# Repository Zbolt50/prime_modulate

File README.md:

# prime_modulate
Firmware for prime_modulate- a split keyboard that has it all, and then more.

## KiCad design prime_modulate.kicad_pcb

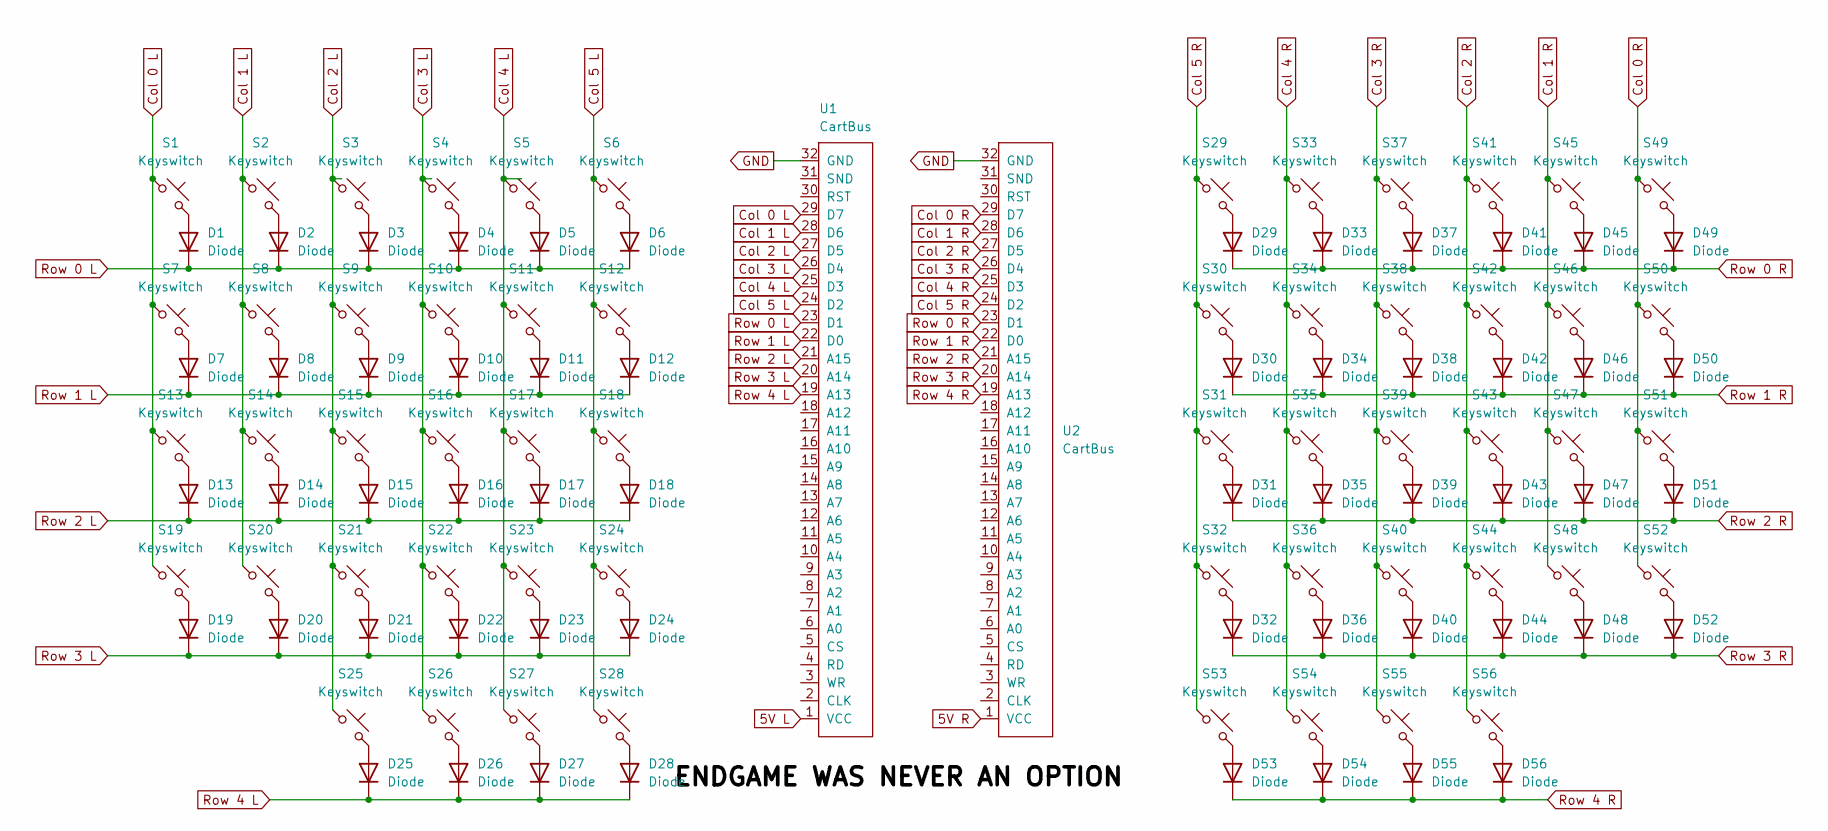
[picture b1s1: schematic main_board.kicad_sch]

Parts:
D1, D2, D3, D4, D5, D6, D7, D8, D9, D10, D11, D12, D13, D14, D15, D16, D17, D18, D19, D20, D21, D22, D23, D24, D25, D26, D27, D28, D29, D30, D31, D32, D33, D34, D35, D36, D37, D38, D39, D40, D41, D42, D43, D44, D45, D46, D47, D48, D49, D50, D51, D52, D53, D54, D55, D56: Diode; Diode_SOD-123
S1, S2, S3, S4, S5, S6, S7, S8, S9, S10, S11, S12, S13, S14, S15, S16, S17, S18, S19, S20, S21, S22, S23, S24, S25, S26, S29, S30, S31, S32, S33, S34, S35, S36, S37, S38, S39, S40, S41, S42, S43, S44, S45, S46, S47, S48, S49, S50, S51, S52, S55, S56: Keyswitch; MXCHOC_Hotswap
S27, S28, S53, S54: Keyswitch; MXCHOC_1.5U_Hotswap
U1, U2: CartBus; DSL_Cartridge_Reader

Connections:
5V L: U1.1 (VCC)
5V R: U2.1 (VCC)
Col 0 L: S1.1, S7.1, S13.1, S19.1, U1.29 (D7)
Col 0 R: S49.1, S50.1, S51.1, S52.1, U2.29 (D7)
Col 1 L: S2.1, S8.1, S14.1, S20.1, U1.28 (D6)
Col 1 R: S45.1, S46.1, S47.1, S48.1, U2.28 (D6)
Col 2 R: S41.1, S42.1, S43.1, S44.1, S56.1, U2.27 (D5)
Col 3 R: S37.1, S38.1, S39.1, S40.1, S55.1, U2.26 (D4)
Col 4 L: S5.1, S11.1, S17.1, S23.1, S27.1, U1.25 (D3)
Col 4 R: S33.1, S34.1, S35.1, S36.1, S54.1, U2.25 (D3)
Col 5 L: S6.1, S12.1, S18.1, S24.1, S28.1, U1.24 (D2)
Col 5 R: S29.1, S30.1, S31.1, S32.1, S53.1, U2.24 (D2)
GND: U1.32 (GND), U2.32 (GND)
unnamed: D1.2 (A), S1.2
unnamed: D2.2 (A), S2.2
unnamed: D3.2 (A), S3.2
unnamed: D4.2 (A), S4.2
unnamed: D5.2 (A), S5.2
unnamed: D6.2 (A), S6.2
unnamed: D7.2 (A), S7.2
unnamed: D8.2 (A), S8.2
unnamed: D9.2 (A), S9.2
unnamed: D10.2 (A), S10.2
unnamed: D11.2 (A), S11.2
unnamed: D12.2 (A), S12.2
unnamed: D13.2 (A), S13.2
unnamed: D14.2 (A), S14.2
unnamed: D15.2 (A), S15.2
unnamed: D16.2 (A), S16.2
unnamed: D17.2 (A), S17.2
unnamed: D18.2 (A), S18.2
unnamed: D19.2 (A), S19.2
unnamed: D20.2 (A), S20.2
unnamed: D21.2 (A), S21.2
unnamed: D22.2 (A), S22.2
unnamed: D23.2 (A), S23.2
unnamed: D24.2 (A), S24.2
unnamed: D26.2 (A), S26.2
unnamed: D25.2 (A), S25.2
unnamed: D27.2 (A), S27.2
unnamed: D28.2 (A), S28.2
unnamed: D29.2 (A), S29.2
unnamed: D30.2 (A), S30.2
unnamed: D31.2 (A), S31.2
unnamed: D32.2 (A), S32.2
unnamed: D33.2 (A), S33.2
unnamed: D34.2 (A), S34.2
unnamed: D35.2 (A), S35.2
unnamed: D36.2 (A), S36.2
unnamed: D37.2 (A), S37.2
unnamed: D38.2 (A), S38.2
unnamed: D39.2 (A), S39.2
unnamed: D40.2 (A), S40.2
unnamed: D41.2 (A), S41.2
unnamed: D42.2 (A), S42.2
unnamed: D43.2 (A), S43.2
unnamed: D44.2 (A), S44.2
unnamed: D45.2 (A), S45.2
unnamed: D46.2 (A), S46.2
unnamed: D47.2 (A), S47.2
unnamed: D48.2 (A), S48.2
unnamed: D49.2 (A), S49.2
unnamed: D50.2 (A), S50.2
unnamed: D51.2 (A), S51.2
unnamed: D52.2 (A), S52.2
unnamed: D53.2 (A), S53.2
unnamed: D54.2 (A), S54.2
unnamed: D55.2 (A), S55.2
unnamed: D56.2 (A), S56.2
Row 0 L: D1.1 (K), D2.1 (K), D3.1 (K), D4.1 (K), D5.1 (K), D6.1 (K), U1.23 (D1)
Row 0 R: D29.1 (K), D33.1 (K), D37.1 (K), D41.1 (K), D45.1 (K), D49.1 (K), U2.23 (D1)
Row 1 L: D7.1 (K), D8.1 (K), D9.1 (K), D10.1 (K), D11.1 (K), D12.1 (K), U1.22 (D0)
Row 1 R: D30.1 (K), D34.1 (K), D38.1 (K), D42.1 (K), D46.1 (K), D50.1 (K), U2.22 (D0)
Row 2 L: D13.1 (K), D14.1 (K), D15.1 (K), D16.1 (K), D17.1 (K), D18.1 (K), U1.21 (A15)
Row 2 R: D31.1 (K), D35.1 (K), D39.1 (K), D43.1 (K), D47.1 (K), D51.1 (K), U2.21 (A15)
Row 3 L: D19.1 (K), D20.1 (K), D21.1 (K), D22.1 (K), D23.1 (K), D24.1 (K), U1.20 (A14)
Row 3 R: D32.1 (K), D36.1 (K), D40.1 (K), D44.1 (K), D48.1 (K), D52.1 (K), U2.20 (A14)
Row 4 L: D25.1 (K), D26.1 (K), D27.1 (K), D28.1 (K), U1.19 (A13)
Row 4 R: D53.1 (K), D54.1 (K), D55.1 (K), D56.1 (K), U2.19 (A13)

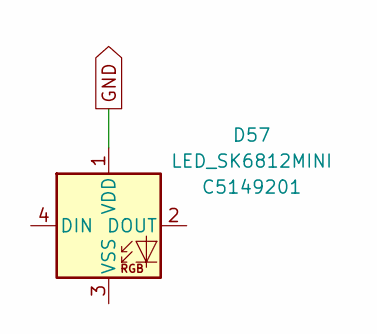
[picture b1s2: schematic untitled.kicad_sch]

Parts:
D57: LED_SK6812MINI; SK6812-MINI-E; LCSC C5149201

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
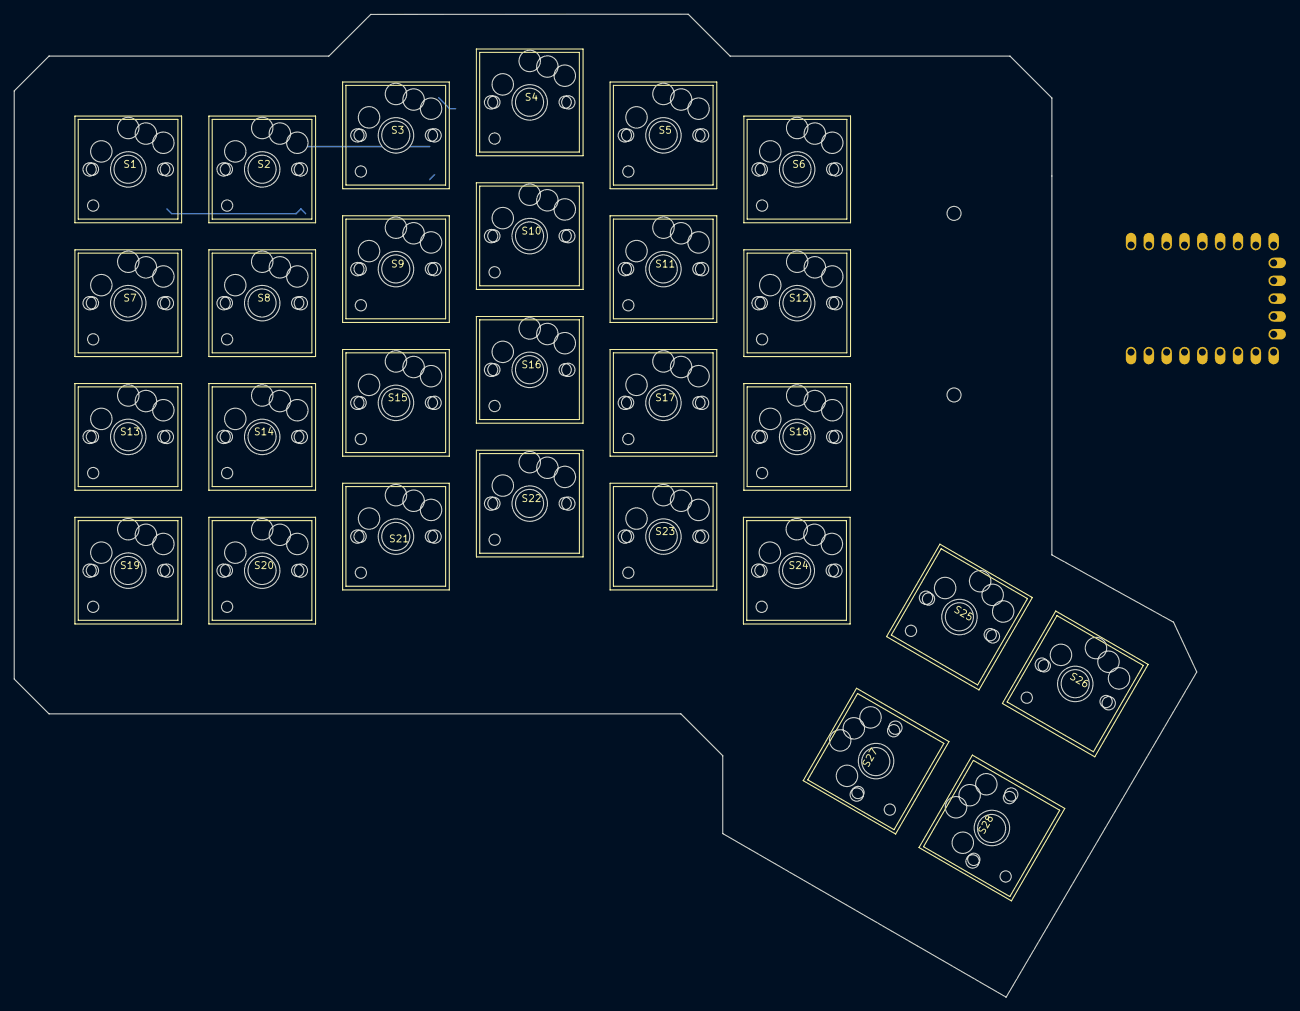
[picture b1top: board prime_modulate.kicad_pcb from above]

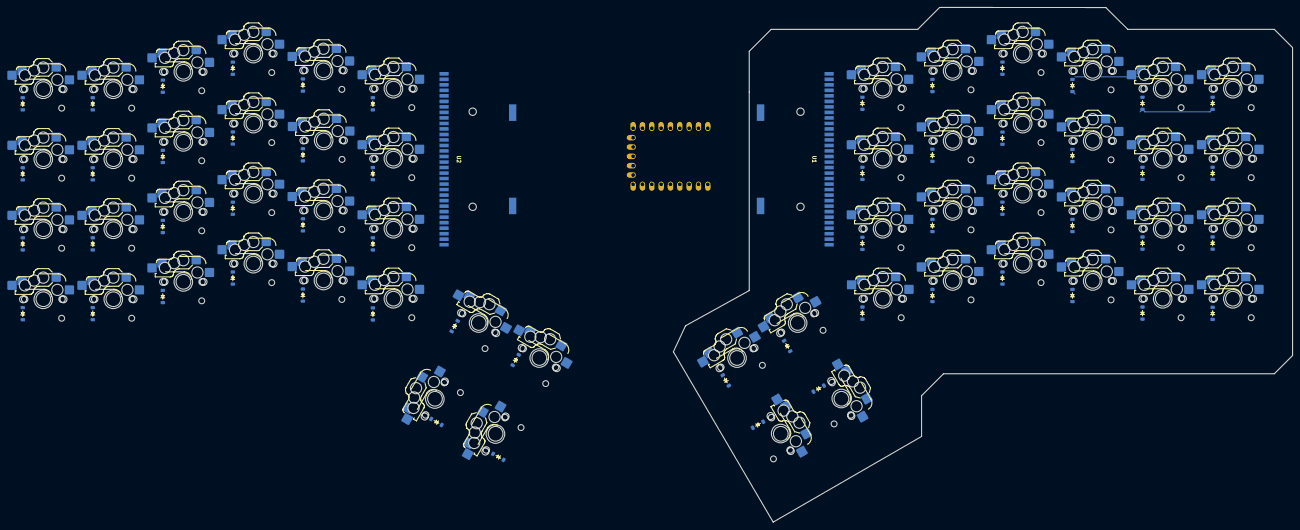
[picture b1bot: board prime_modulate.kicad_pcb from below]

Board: 2 copper layers, 168.4 x 140.0 mm, 115 parts (58 on the bottom side), 79 nets.

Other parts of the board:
U?: RP2040_Zero

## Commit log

2024-12-23 Initial Board Files
2024-12-24 First Major Board design, updated footprints with 3D models to be commited later
2024-12-28 added other files
2024-12-29 Changed board outline
